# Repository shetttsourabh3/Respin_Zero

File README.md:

<p align="center">

</p>

<p align="center">
  <b>Get your board right the first time.</b><br>
  A KiCad plugin that takes your board from design rules to fabrication files, with a review at every step.<br>
  Built for embedded engineers who design boards but are not full-time PCB specialists.
</p>

<p align="center">
  <a href="#install">Install</a> ·
  <a href="#features">Features</a> ·
  <a href="#quick-start">Quick start</a> ·
  <a href="#ai-review-optional">AI review</a> ·
  <a href="docs/user-guide.md">User guide</a> ·
  <a href="#roadmap">Roadmap</a> ·
  <a href="CONTRIBUTING.md">Contributing</a>
</p>

---

## Why

Most board re-spins come from a short list of mistakes: a strapping pin pulled the wrong way, a missing pull-up, a crystal with the wrong frequency, a track too thin for its current, a clearance the fabricator cannot make. KiCad's ERC and DRC catch some of them. Respin Zero catches more, explains each one in plain language, and will not let you send files to the fabricator until the blocking ones are fixed or consciously waived.

**Respin Zero** is named after the goal: zero re-spins. It is **one window** inside KiCad, organised in the order you work: **Set up → Review → Release**.

## Features

### Set up
- **Design rules from a few questions.** IPC-2221 spacing and conductor widths, IPC-6012 class, copper weights and board thickness. Every generated rule shows *why* it has that value.
- **Fabricator profiles** for JLCPCB, PCBWay, NextPCB, PCB Power and Lion Circuits (India and China). Rules never go below what your fabricator can make.
- **Beginner, Intermediate and Expert levels.** Beginners get the main questions and explanations; experts can override everything.
- **Nets and currents.** Power, ground and high-voltage nets are found from their names; give a current and get per-net width and clearance rules.
- **Datasheet library** per project, organised in category folders, with the exact part number of each part.

### Review
- **Schematic review** with generic checks (decoupling, I2C pull-ups, USB-C CC resistors, USB ESD, LED current, crystal load capacitors) and **chip profiles** for ESP32-C3, RP2040 and STM32F1 (boot and strapping pins, reset RC, supply range, crystal frequency, debug access). Profiles are JSON files: add your own.
- **ERC and DRC** through `kicad-cli`, sorted into *Blocks fabrication*, *Reliability risk* and *Cosmetic*, each with a fix and the reason it matters.
- **Power and thermal**: track temperature rise, vias per layer change, worst-case voltage drop and thermal-pad vias for every power net.
- **Readable results**: plain titles, filter chips, group by part, a detail card with *what is wrong / how to fix / why it matters*, and a warning when results are out of date.
- **Waivers with a reason**, kept in an audit file you can commit.

| Group findings by part | ERC / DRC explained |
|---|---|
|  |  |

### Release
- **Production files in one click**: Gerbers and drill files in one zip, position file and BOM, in JLCPCB, PCBWay or generic format.
- **Fabrication gate**: final checks (all reviews run on the latest saved files, no blocking findings, outline, layers and thickness within the fabricator's range, every part on the board), then the files and a fab note, saved as a *Sent to fab* version.
- **History with Git**: save versions with milestones, push and pull with your own Git sign-in, a timeline of review progress, and **Compare** two versions (findings fixed and new, parts and nets changed).

| Fabrication gate | History timeline |
|---|---|
|  |  |

### Works with you
- **Sidebar with live status** for every step, keyboard shortcuts (`Ctrl+1…0`, `Ctrl+R`), light and dark mode.
- **Works beside the Schematic Editor** through a desktop launcher (KiCad 10 shows plugins only in the PCB editor).
- **Report a problem** builds a bug report with versions and logs, and no design data.

## Install

**Requirements:** KiCad **10.0** or newer (10.x) on Windows, macOS or Linux. Optional: [Git](https://git-scm.com/) for History, and an AI tool for the AI review.

### From a release (recommended)
1. Download `respin_zero-<version>.zip` from the [latest release](https://github.com/YOUR-GITHUB-USERNAME/respin-zero/releases). Do **not** unzip it.
2. In KiCad, open **Plugin and Content Manager**.
3. Click **Install from File...** and choose the zip.
4. Open your board in the **PCB Editor**. The **Respin Zero** button is on the toolbar.

### From source
```bash
git clone https://github.com/YOUR-GITHUB-USERNAME/respin-zero.git
cd respin-zero
python3 tools/build_zip.py        # writes dist/respin_zero-<version>.zip
```
Then install the zip as above.

### Use it while you work on the schematic
On the **Overview** page press **Shortcut for schematic work...** once. It puts a launcher for the project on your desktop that opens the same window without the PCB editor.

## Quick start

1. **Design rules**: answer the questions, choose your fabricator, press **Apply rules**.
2. **Nets & currents**: give currents to your power nets.
3. Press **Run all checks** (`Ctrl+R`). Fix the red findings first; waive with a reason only what you have checked.
4. **Production files** at any time for a quick quote, or **Fabrication** when you release: final checks, files, and a version.
5. **History**: **Push** to keep the design and its review state on GitHub or GitLab.

The full walk-through is in the [user guide](docs/user-guide.md).

## AI review (optional)

The AI review is **off until you use it** and works with **any AI tool**, using **your own account or a model on your own computer**:

| Tool | Datasheets | Account |
|---|---|---|
| Claude Code | reads the PDFs | Claude Pro / Max |
| OpenAI Codex CLI | page text | ChatGPT account |
| `llm` CLI | page text | OpenAI, Gemini, Mistral, local models… |
| Ollama / LM Studio / llama.cpp (local) | page text | none, runs on your computer |
| Your own command-line tool | your choice | your choice |

**Privacy by design**
- The plugin **never asks for, stores or sends a password, key or token**. Each tool uses its own sign-in.
- **What is sent?** shows the exact text before you send anything. **Never send this project to AI** turns it off per project.
- Tools run without shell access, in an empty temporary folder.
- Every AI finding must name parts, pins or nets that exist in the design, or it is dropped. A low-confidence finding never blocks fabrication.
- For each datasheet, only the pages that matter for the **exact part number** are sent (pin description, absolute maximum ratings, ordering code, application circuit).

AI findings can be wrong. They are marked **AI**, show their confidence, and should be checked against the datasheet.

## Files it creates in your project

| File | Content |
|---|---|
| `<project>.kicad_dru` | Generated rules between marker lines. Your own rules below the markers are kept. |
| `ipc_ste_requirements.json` | Your answers and net groups. |
| `ipc_ste_waivers.json` | Waivers with reason, user and date (commit it). |
| `datasheets/` | The datasheet library. |
| `production/`, `fab/<version>/` | Production and fabrication files. |
| `.respin_zero/findings.json` | Review state of each saved version, for **Compare**. |

## Limits

- **Beta.** Tested with automated tests and on Linux; please report problems on Windows and macOS with **Report a problem**.
- The fabricator BOM and pick-and-place formats follow the fabricators' published upload guides. **Check part rotations in the fabricator's preview** before you order assembly.
- IPC-2221 values are conservative minimums. For mains or patient-connected circuits use IEC 62368-1 or IEC 60601-1 creepage and clearance.
- Fabricator capability values were copied from public pages; check them before you order.
- KiCad 10 does not let plugins change the stackup directly; the plugin edits the board file and you use **File > Revert**.

## Roadmap

- **KiCad 11 support** through KiCad's IPC API, including the Schematic Editor ([plan](docs/roadmap.md)). KiCad 10 stays supported.
- More chip profiles: ESP32-S3, ESP32-C6, nRF52, STM32G0/C0, RP2350, CH32V.
- Medical and safety skill pack (IEC 60601 creepage and clearance, isolation checks).
- Part-number and footprint consistency checks for assembly.

Ideas and votes are welcome in [Discussions](https://github.com/YOUR-GITHUB-USERNAME/respin-zero/discussions).

## Related projects

Respin Zero focuses on a guided, in-KiCad workflow with deterministic checks first and AI as an option. Other good tools you may want next to it:
[kicad-happy](https://github.com/aklofas/kicad-happy) (AI agent skills for deep analysis),
[Konnect](https://github.com/mixelpixx/Konnect) (AI-assisted design over MCP),
[Fabrication Toolkit](https://github.com/bennymeg/Fabrication-Toolkit) and
[KiBot](https://github.com/INTI-CMNB/KiBot) (fabrication outputs and CI).

## Contributing

Bug reports, chip profiles, fabricator formats and translations are all welcome. Read [CONTRIBUTING.md](CONTRIBUTING.md) to get started and the [Code of Conduct](CODE_OF_CONDUCT.md). Security or privacy issue? See [SECURITY.md](SECURITY.md).

## License

[MIT](LICENSE) © 2026 Sourabh Shetty. Bundled third-party code is listed in [THIRD_PARTY_NOTICES.md](THIRD_PARTY_NOTICES.md).

KiCad is a trademark of the KiCad project. This plugin is not affiliated with or endorsed by the KiCad project or by any fabricator named here.

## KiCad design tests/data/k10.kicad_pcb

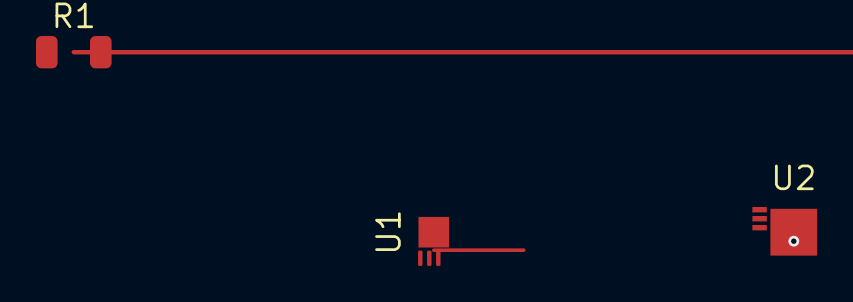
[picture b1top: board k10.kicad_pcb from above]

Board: 4 copper layers, 3 parts (0 on the bottom side), 3 nets.

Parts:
R1: R_1206
U1: QFN-16-1EP_3x3mm
U2: QFN-24-1EP_4x4mm

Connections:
+5V: R1.2, U1.1
/SDA: U1.2, U2.2
GND: R1.1, U1.3, U1.17, U2.3, U2.25

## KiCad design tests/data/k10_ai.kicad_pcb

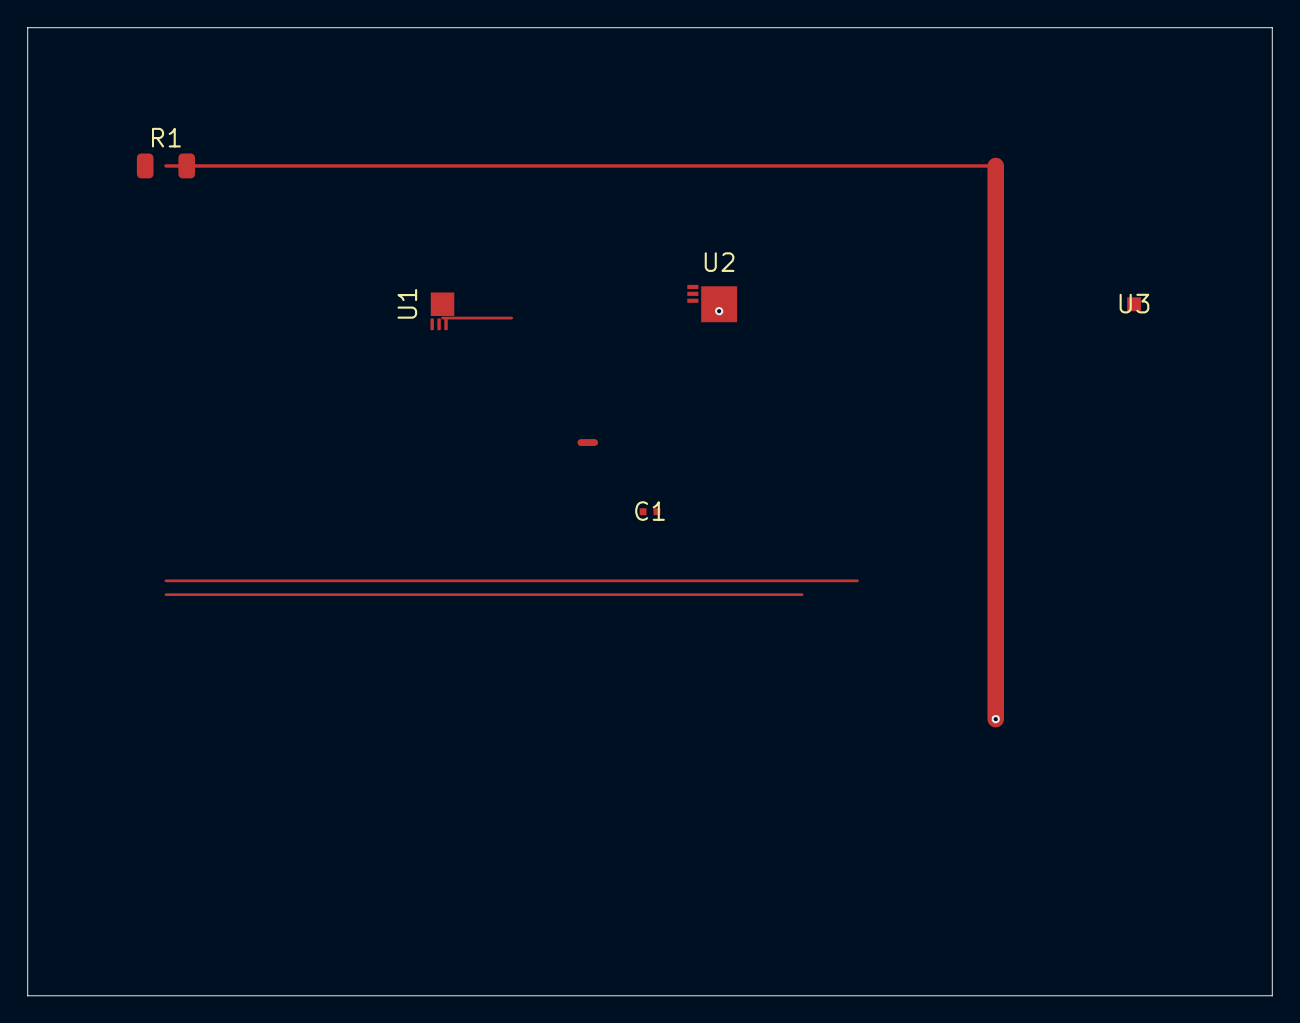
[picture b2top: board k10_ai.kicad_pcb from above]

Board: 4 copper layers, 90.0 x 70.0 mm, 5 parts (0 on the bottom side), 3 nets.

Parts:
C1: 100n; C_0402
R1: R_1206
U1: QFN-16-1EP_3x3mm
U2: QFN-24-1EP_4x4mm
U3: ESP32-C3-MINI-1

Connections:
+5V: C1.1, R1.2, U1.1
/SDA: U1.2, U2.2
GND: C1.2, R1.1, U1.3, U1.17, U2.3, U2.25, U3.1
